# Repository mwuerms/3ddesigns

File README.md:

# 3ddesigns
collection of different 3d models

freepiston
----------- 

Started a design of a freep piston stirling engine, low temperature difference

using openscad

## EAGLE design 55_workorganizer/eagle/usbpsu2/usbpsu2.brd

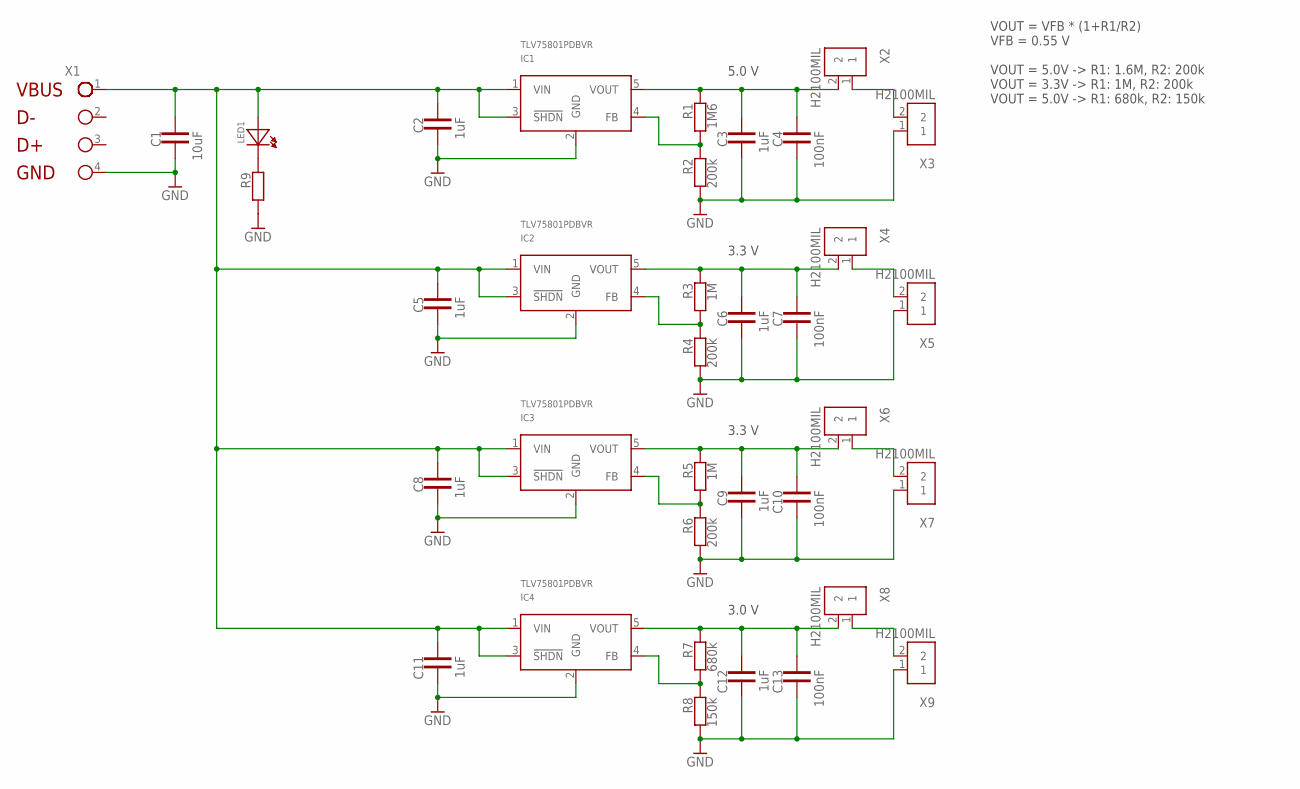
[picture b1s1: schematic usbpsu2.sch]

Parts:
C1: 10uF; 0805MIL
C2, C3, C5, C6, C8, C9, C11, C12: 1uF; 0805MIL
C4, C7, C10, C13: 100nF; 0603MIL
IC1, IC2, IC3, IC4: TLV75801PDBVR; SOT23-5_2
LED1: LED0603; 0603MIL_POL
R1: 1M6; 0603MIL
R2, R4, R6: 200k; 0603MIL
R3, R5: 1M; 0603MIL
R7: 680k; 0603MIL
R8: 150k; 0603MIL
R9: R0603; 0603MIL
X1: H4USB; HEADER4_100MIL
X2, X3, X4, X5, X6, X7, X8, X9: H2100MIL; HEADER2_100MIL

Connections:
GND: C1.2, C2.2, C3.2, C4.2, C5.2, C6.2, C7.2, C8.2, C9.2, C10.2, C11.2, C12.2, C13.2, IC1.2 (GND), IC2.2 (GND), IC3.2 (GND), IC4.2 (GND), R2.2, R4.2, R6.2, R8.2, R9.2, X1.4 (GND), X3.1, X5.1, X7.1, X9.1
unnamed: LED1.2 (K), R9.1
VBUS: C1.1, C2.1, C5.1, C8.1, C11.1, IC1.1 (VIN), IC1.3 (!SHDN), IC2.1 (VIN), IC2.3 (!SHDN), IC3.1 (VIN), IC3.3 (!SHDN), IC4.1 (VIN), IC4.3 (!SHDN), LED1.1 (A), X1.1 (VBUS)
VFB1: IC1.4 (FB), R1.2, R2.1
VFB2: IC2.4 (FB), R3.2, R4.1
VFB3: IC3.4 (FB), R5.2, R6.1
VFB4: IC4.4 (FB), R7.2, R8.1
VOUT1: X2.1, X3.2
VOUT1A: C3.1, C4.1, IC1.5 (VOUT), R1.1, X2.2
VOUT2: X4.1, X5.2
VOUT2A: C6.1, C7.1, IC2.5 (VOUT), R3.1, X4.2
VOUT3: X6.1, X7.2
VOUT3A: C9.1, C10.1, IC3.5 (VOUT), R5.1, X6.2
VOUT4: X8.1, X9.2
VOUT4A: C12.1, C13.1, IC4.5 (VOUT), R7.1, X8.2

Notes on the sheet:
VOUT = VFB * (1+R1/R2) VFB = 0.55 V VOUT = 5.0V -> R1: 1.6M, R2: 200k VOUT = 3.3V -> R1: 1M, R2: 200k VOUT = 5.0V -> R1: 680k, R2: 150k
3.0 V
3.3 V
5.0 V

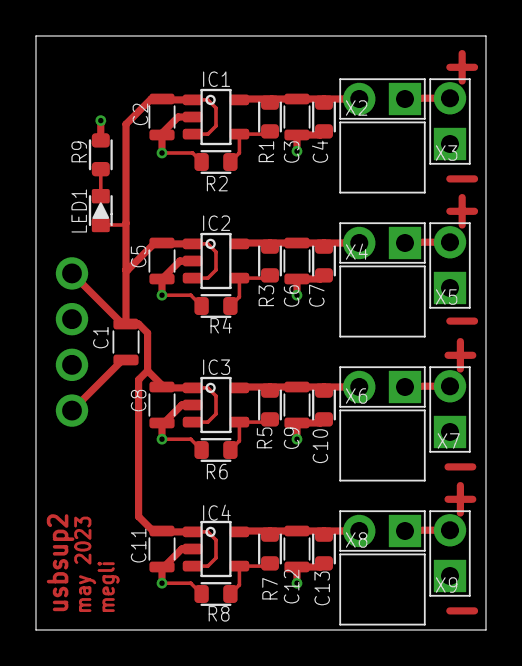
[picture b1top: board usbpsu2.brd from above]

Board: 2 copper layers, 25.0 x 33.0 mm, 36 parts (0 on the bottom side), 15 nets.

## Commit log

2019-09-07 started a free piston stirling engine
2019-09-09 changed spring and displacer holder
2020-09-26 schnapper added
2020-09-28 added
2020-09-28 additional holderE added
2020-09-28 started
2020-09-29 holder2 minor adjustments
2021-05-20 bitvoodoo domino stone
2021-06-04 bvDimino for 1 ... 6
2021-07-17 07 heicho dino
2021-08-22 replacement tip kick hat
2021-09-15 heicho dino verbessert + Schoggigussform "Jonas' Idee" erstellt
2021-09-15 chocolateCasting: mold vervbessert
2021-09-29 lots and lots of chocolate designs
2021-10-06 lego v3: this one works, create mold from v3, BUT: do scale before exporting to *.stl
2021-10-16 12 lego molds 14 very simple wheel for toy cart 15 pcb vise
2021-10-17 15 update pcbvise
2021-11-03 03: new laptop holder 12 new lego figurine 16: additional holder for a garderobe
2021-11-12 18 Energy Harvesting inside a AAA Battery case
2021-11-25 singblume done
2021-12-01 21 psu case added
2021-12-08 case for vibra alarm v2
2022-02-11 day chef helper star like a sherrif star
2022-07-07 added "zwinge" + several others
2022-11-27 schirmhalter
2022-11-27 added shupplyholder
2022-11-27 vibraAlarm arduino code added
2022-11-27 added all 3ddesigns from my linux machine, starting from 39_...
2023-01-06 magnetig pcb holder, from thingiverse:39519, changed to sport N5x5x5 neodymium magnets
2023-03-01 v1.0 toothbrush holder
2023-05-20 added minecraft arrow + edge connector for a "Regal"
2023-05-21 workorganizer: arrange electronics tools on a tablet
2023-08-30 56_testing new rotary timer case
2023-09-01 me57 xyz pencil holder
2023-09-03 me57 update v1.1
2023-09-10 calendar holder for under a whiteboard
2023-09-10 58: 1st version of holder, cut in 2
2023-10-22 59_chargerstand
2024-02-27 60 naiholder done, please print
2024-04-14 added button to minivac
2024-04-14 added prusa+stl files
2024-04-15 vl53l1x gaskets added
2024-04-16 62_vl53 glay 1.5/220 adapter added
2024-04-17 added j5050 holder, but not exactly to size
2024-05-05 started 8cm version of the fume extractor (sucker)
2024-05-31 me110 8cm: added M5 mounting nut
2024-06-05 me110: added a clamp for M5 ball head screws
2024-06-06 template for z fine tuning
2024-06-06 doubled x/y size
2024-06-10 part5 -> part5a/part5b, top and bottom part, also using M3 instead of M5 screw, also smaller
2024-06-10 changed to m3 shink head screw
2024-06-10 Merge branch 'master' of github.com:mwuerms/3ddesigns
    dieser
2024-06-12 added a stand
2024-06-13 added a microscope holder
2024-06-27 started the shed project
2024-06-30 64 1st version done
2024-09-06 66 metal bender v1
2024-09-06 added skater wheel holder
2024-09-06 prepared for printing
2024-09-08 use M8 screw as axle
2024-09-17 angle stop 25° and 30° added
2024-10-20 started this box, no idea for the backside yet
2025-02-08 fume extractor v1.0 in freecad
2025-02-09 50a msr fume extractor v1.1
2025-02-09 50a added prusa file
2025-02-09 50a fume extractor v1.2
2025-02-09 50a v1.2a of bottom part
